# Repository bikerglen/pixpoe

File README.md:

# pixpoe
Control and power up to 20 W of neopixels or other WS2812b LEDs over ethernet!

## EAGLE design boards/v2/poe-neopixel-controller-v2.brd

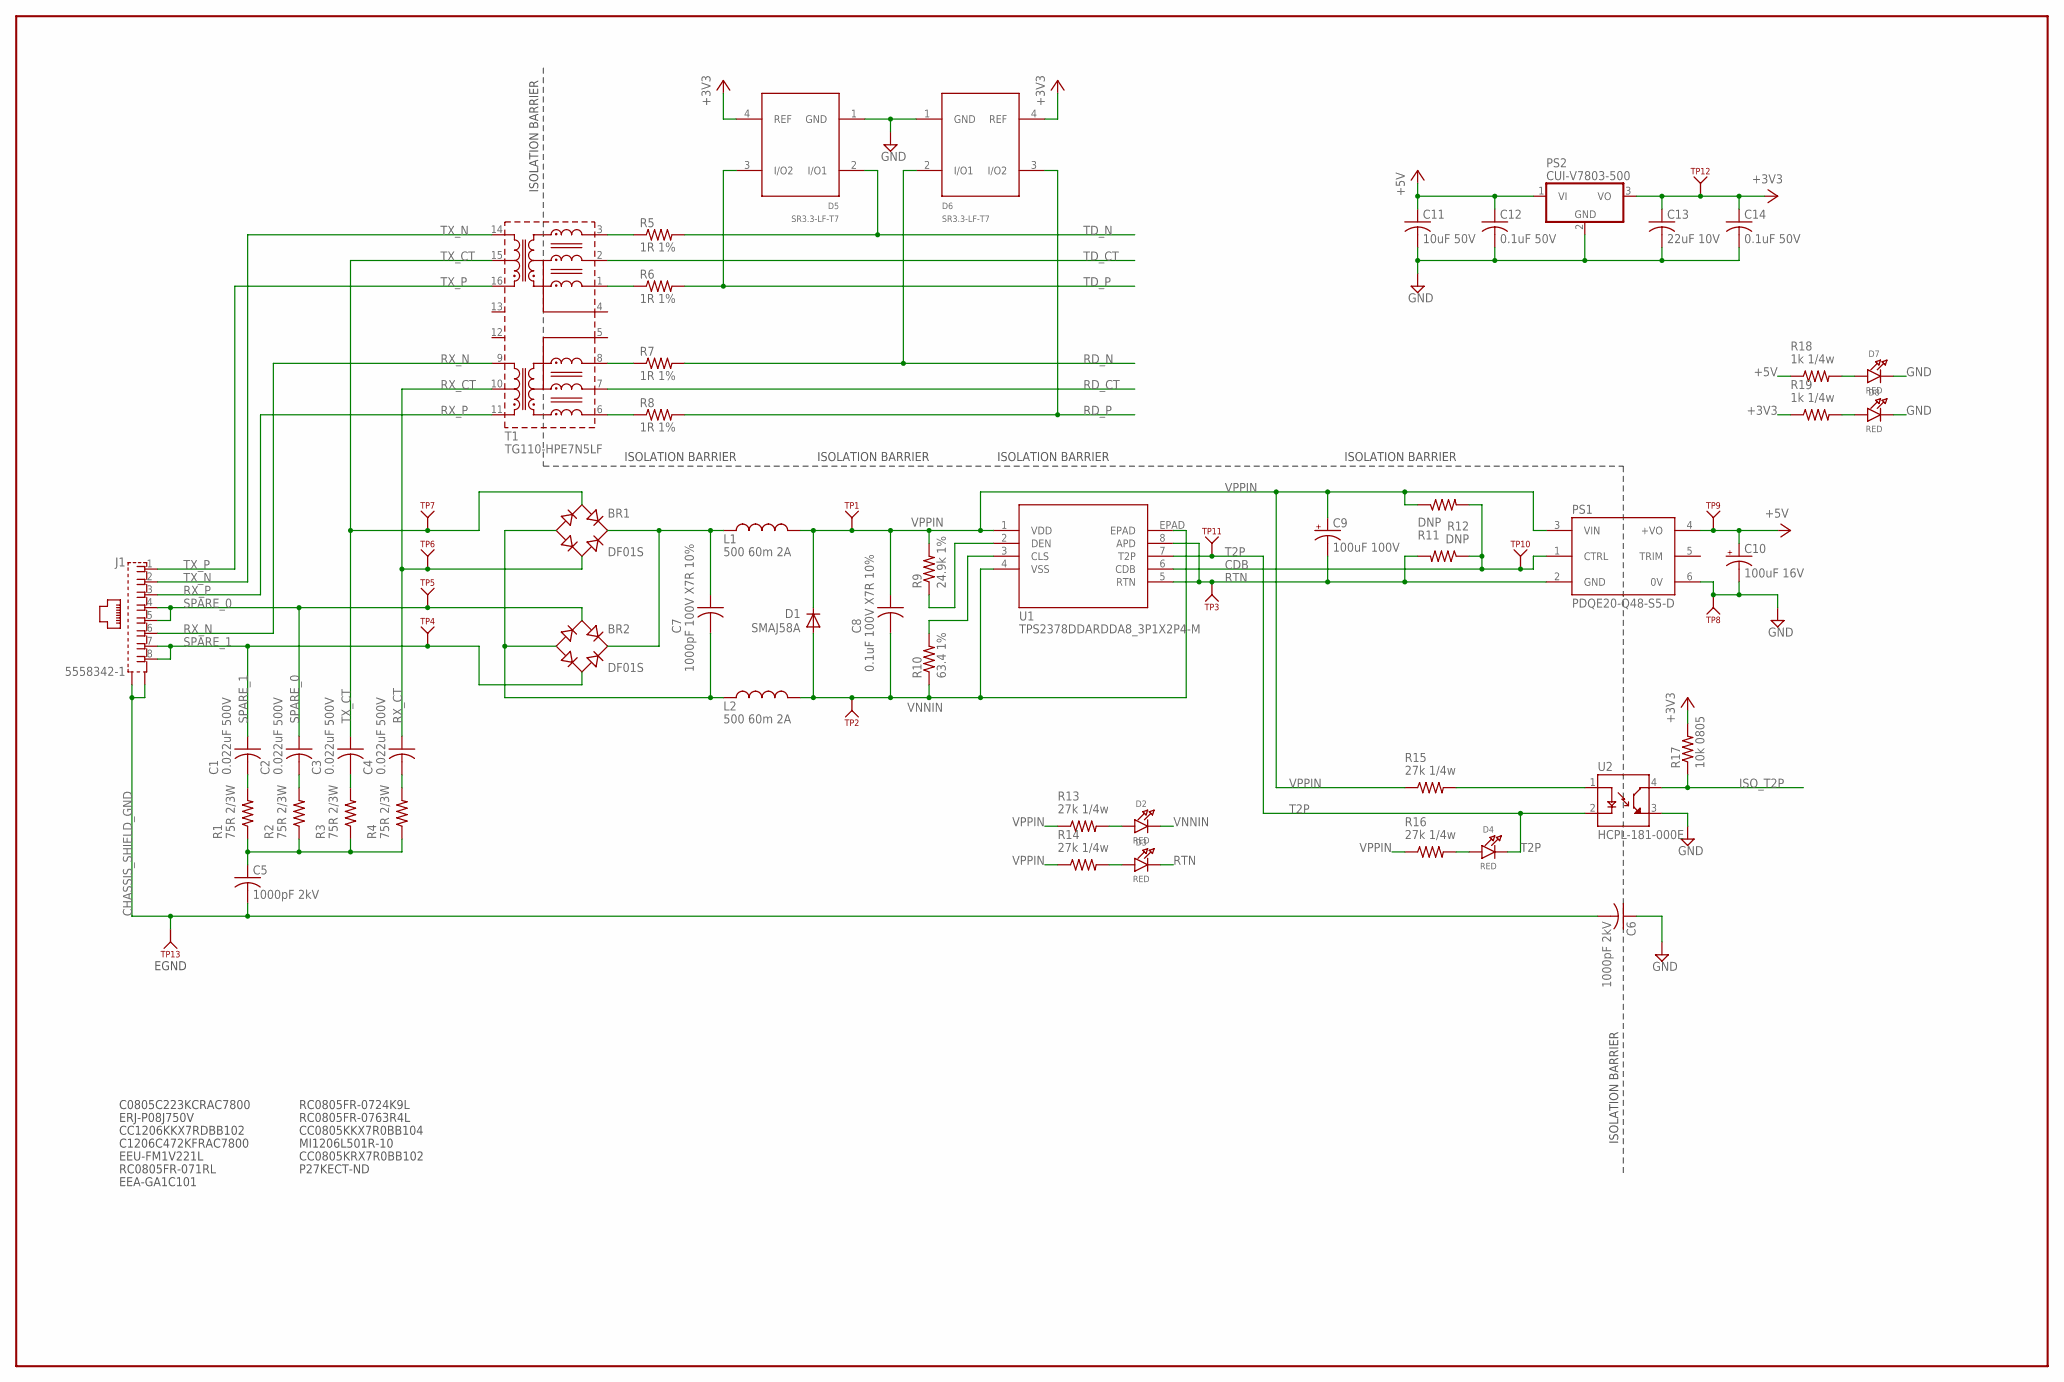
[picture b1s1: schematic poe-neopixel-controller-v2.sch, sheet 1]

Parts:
BR1, BR2: DF01S; DFS
C1, C2, C3, C4: 0.022uF 500V; C1206
C5, C6: 1000pF 2kV; C1206K
C7: 1000pF 100V X7R 10%; C0805
C8: 0.1uF 100V X7R 10%; C0805
C9: 100uF 100V; E5-10,5
C10: 100uF 16V; E2,5-7
C11: 10uF 50V; C1210K; MFR_PART_NO C1210C106K5RACTU
C12, C14: 0.1uF 50V; C0805; MFR_PART_NO C1206S104M5RACTU
C13: 22uF 10V; C1206K; MFR_PART_NO C1206C226K8RAC7800
D1: SMAJ58A; DO214AC
D2, D3, D4, D7, D8: RED; CHIPLED_0805_NOOUTLINE
D5, D6: SR3.3-LF-T7; SOT143B
J1: 5558342-1; TE_5558342-1
L1, L2: 500 60m 2A; L3216C
PS1: PDQE20-Q48-S5-D; CONV_PDQE20-Q48-S5-D
PS2: CUI-V7803-500; CUI-78XX-500
R1, R2, R3, R4: 75R 2/3W; R1206
R5, R6, R7, R8: 1R 1%; R0805
R9: 24.9k 1%; R0805
R10: 63.4 1%; R0805
R11, R12: DNP; R1206
R13, R14, R15, R16: 27k 1/4w; R1206
R17: 10k 0805; R0805
R18, R19: 1k 1/4w; R0805
T1: TG110-HPE7N5LF; RP-ULTRA
TP1, TP2, TP3, TP4, TP5, TP6, TP7, TP8, TP9, TP10, TP11, TP12, TP13: KEYSTONE_500X; KEYSTONE_TP500X
U1: TPS2378DDARDDA8_3P1X2P4-M; DDA8_3P1X2P4-M
U2: HCPL-181-000E; SOIC254P675X240-4N

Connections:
+3V3: C13.1, C14.1, D5.4 (REF), D6.4 (REF), PS2.3 (VO), R17.2, R19.1, TP12.1; also elsewhere on the board
+5V: C10.+, C11.1, C12.1, PS1.4 (+VO), PS2.1 (VI), R18.1, TP9.1; also elsewhere on the board
CDB: PS1.1 (CTRL), R11.2, R12.1, TP10.1, U1.6 (CDB)
CHASSIS_SHIELD_GND: C5.2, C6.2, J1.SH1 (S1), J1.SH2 (S2), TP13.1
GND: C6.1, C10.-, C11.2, C12.2, C13.2, C14.2, D5.1 (GND), D6.1 (GND), D7.C, D8.C, PS1.6 (0V), PS2.2 (GND), TP8.1, U2.3 (EMITTER); also elsewhere on the board
ISO_T2P: R17.1, U2.4 (COLLECTOR); also elsewhere on the board
unnamed: BR1.+, BR2.+, C7.1, L1.1
unnamed: R5.1, T1.3
unnamed: BR1.-, BR2.-, C7.2, L2.1
unnamed: R6.1, T1.1
unnamed: C4.2, R4.2
unnamed: R7.1, T1.8
unnamed: D2.A, R13.2
unnamed: R15.2, U2.1 (ANODE)
unnamed: R8.1, T1.6
unnamed: C1.2, R1.2
unnamed: C2.2, R2.2
unnamed: C3.2, R3.2
unnamed: C5.1, R1.1, R2.1, R3.1, R4.1
unnamed: R9.1, U1.2 (DEN)
unnamed: R10.2, U1.3 (CLS)
unnamed: D3.A, R14.2
unnamed: D4.A, R16.2
unnamed: D7.A, R18.2
unnamed: D8.A, R19.2
RD_CT: T1.7; also elsewhere on the board
RD_N: D6.2 (I/O1), R7.2; also elsewhere on the board
RD_P: D6.3 (I/O2), R8.2; also elsewhere on the board
RTN: C9.-, D3.C, PS1.2 (GND), R12.2, TP3.1, U1.5 (RTN), U1.8 (APD)
RX_CT: BR1.AC2, C4.1, T1.10, TP6.1
RX_N: J1.6, T1.9
RX_P: J1.3, T1.11
SPARE_0: BR2.AC1, C2.1, J1.4, J1.5, TP5.1
SPARE_1: BR2.AC2, C1.1, J1.7, J1.8, TP4.1
T2P: D4.C, TP11.1, U1.7 (T2P), U2.2 (CATHODE)
TD_CT: T1.2; also elsewhere on the board
TD_N: D5.2 (I/O1), R5.2; also elsewhere on the board
TD_P: D5.3 (I/O2), R6.2; also elsewhere on the board
TX_CT: BR1.AC1, C3.1, T1.15, TP7.1
TX_N: J1.2, T1.14
TX_P: J1.1, T1.16
VNNIN: C8.2, D1.A, D2.C, L2.2, R10.1, TP2.1, U1.4 (VSS), U1.EPAD
VPPIN: C8.1, C9.+, D1.C, L1.2, PS1.3 (VIN), R9.2, R11.1, R13.1, R14.1, R15.1, R16.1, TP1.1, U1.1 (VDD)

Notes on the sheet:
C0805C223KCRAC7800
ERJ-P08J750V
CC1206KKX7RDBB102
C1206C472KFRAC7800
EEU-FM1V221L
ISOLATION BARRIER
RC0805FR-071RL
EEA-GA1C101
RC0805FR-0724K9L
RC0805FR-0763R4L
CC0805KKX7R0BB104
MI1206L501R-10
CC0805KRX7R0BB102
P27KECT-ND
EGND

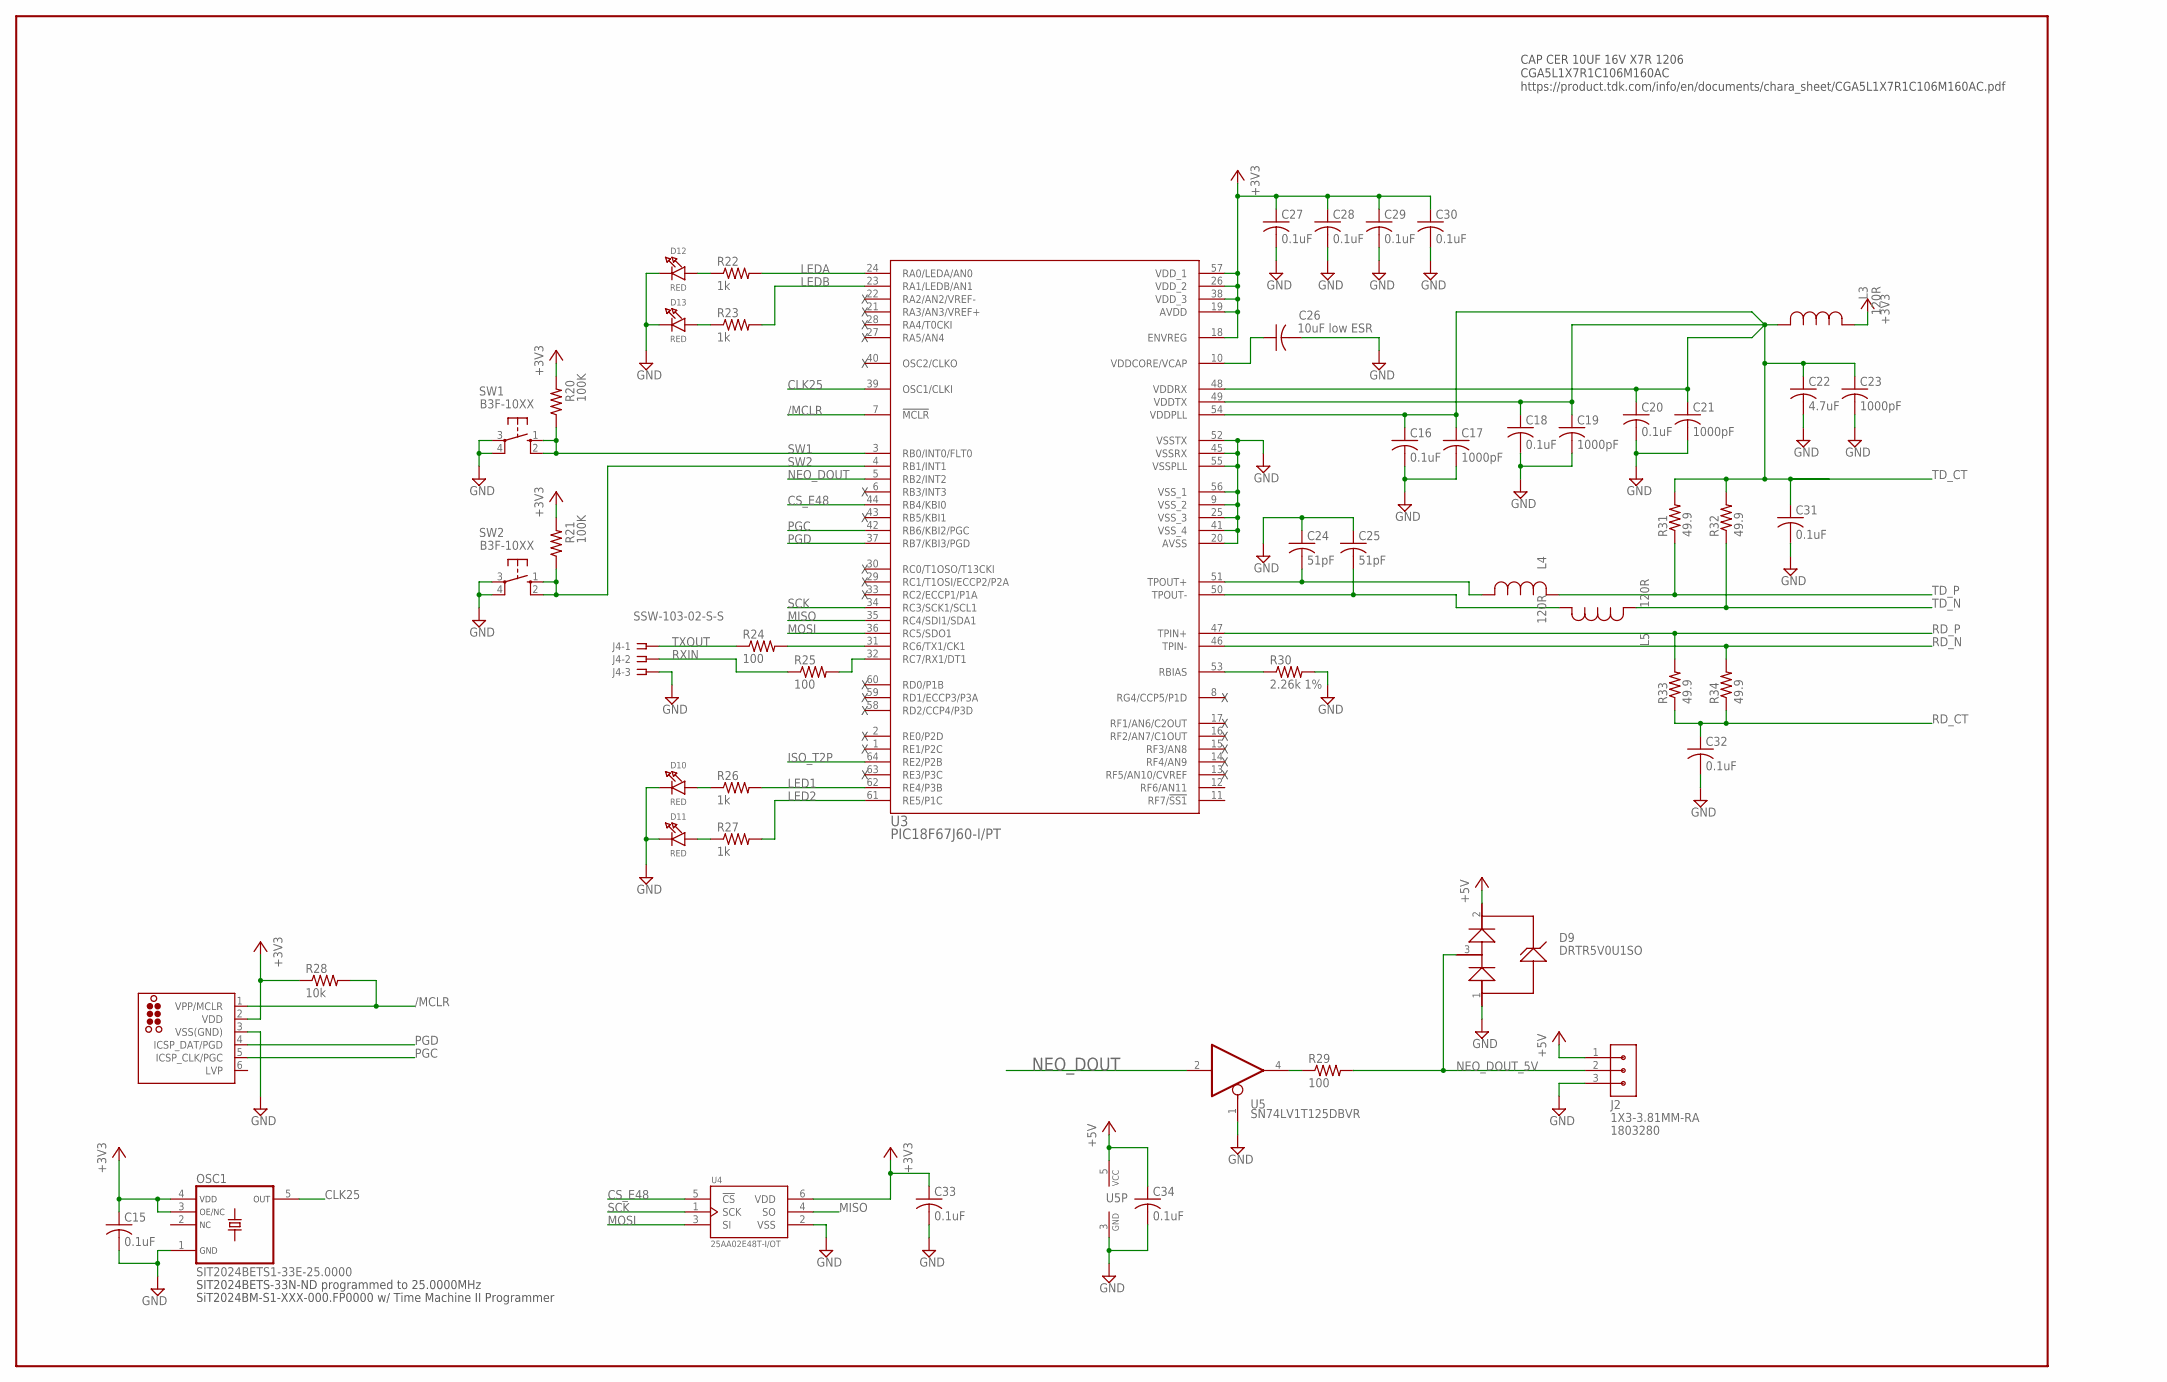
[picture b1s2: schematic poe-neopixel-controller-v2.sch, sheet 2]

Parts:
C15, C27, C28, C29, C30, C33, C34: 0.1uF; C0603
C16, C18, C20, C31, C32: 0.1uF; C0805
C17, C19, C21, C23: 1000pF; C0805
C22: 4.7uF; C0805
C24, C25: 51pF; C0805
C26: 10uF low ESR; C1206
D9: DRTR5V0U1SO; SOT23-3; MFR_PART_NO DRTR5V0U1SO
D10, D11, D12, D13: RED; CHIPLED_0805_NOOUTLINE
J2: 1X3-3.81MM-RA; CON-PHOENIX-3.81-1X3-RA; MFR_PART_NO 1803280
J3: TC2030-MCP-NL
J4: SSW-103-02-S-S
L3, L4, L5: 120R; IND_1608-M
OSC1: SIT2024BETS1-33E-25.0000; SOT23-5
R20, R21: 100K; R0805
R22, R23, R26, R27: 1k; R0805
R24, R25, R29: 100; R0805
R28: 10k; R0805
R30: 2.26k 1%; R0805
R31, R32, R33, R34: 49.9; R0805
SW1, SW2: B3F-10XX
U3: PIC18F67J60-I/PT; TQFP64_10X10MC
U4: 25AA02E48T-I/OT; SOT95P270X145-6N
U5: SN74LV1T125DBVR; SOT23-5; MFR_PART_NO SN74LV1T125DBVR

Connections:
+3V3: C15.1, C27.1, C28.1, C29.1, C30.1, C33.1, J3.2 (VDD), L3.2, OSC1.3 (OE/NC), OSC1.4 (VDD), R20.2, R21.2, R28.1, U3.18 (ENVREG), U3.19 (AVDD), U3.26 (VDD_2), U3.38 (VDD_3), U3.57 (VDD_1), U4.6 (VDD); also elsewhere on the board
+5V: C34.1, D9.2, J2.1, U5.5 (VCC); also elsewhere on the board
/MCLR: J3.1 (VPP/MCLR), R28.2, U3.7 (!MCLR)
CLK25: OSC1.5 (OUT), U3.39 (OSC1/CLKI)
CS_E48: U3.44 (RB4/KBI0), U4.5 (!CS)
DATA_5V: R29.1, U5.4 (O)
GND: C15.2, C16.2, C17.2, C18.2, C19.2, C20.2, C21.2, C22.2, C23.2, C24.1, C25.1, C26.2, C27.2, C28.2, C29.2, C30.2, C31.2, C32.2, C33.2, C34.2, D9.1 (3), D10.C, D11.C, D12.C, D13.C, J2.3, J3.3 (VSS(GND)), J4.3, OSC1.1 (GND), R30.2, SW1.3, SW1.4 (P1), SW2.3, SW2.4 (P1), U3.9 (VSS_2), U3.20 (AVSS), U3.25 (VSS_3), U3.41 (VSS_4), U3.45 (VSSRX), U3.52 (VSSTX), U3.55 (VSSPLL), U3.56 (VSS_1), U4.2 (VSS), U5.1 (OE), U5.3 (GND); also elsewhere on the board
ISO_T2P: U3.64 (RE2/P2B); also elsewhere on the board
LED1: R26.2, U3.62 (RE4/P3B)
LED2: R27.2, U3.61 (RE5/P1C)
LEDA: R22.2, U3.24 (RA0/LEDA/AN0)
LEDB: R23.2, U3.23 (RA1/LEDB/AN1)
MISO: U3.35 (RC4/SDI1/SDA1), U4.4 (SO)
MOSI: U3.36 (RC5/SDO1), U4.3 (SI)
unnamed: C26.1, U3.10 (VDDCORE/VCAP)
unnamed: R30.1, U3.53 (RBIAS)
unnamed: D13.A, R23.1
unnamed: D10.A, R26.1
unnamed: D11.A, R27.1
unnamed: D12.A, R22.1
NEO_DOUT: U3.5 (RB2/INT2), U5.2 (I)
NEO_DOUT_5V: D9.3 (1), J2.2, R29.2
PGC: J3.5 (ICSP_CLK/PGC), U3.42 (RB6/KBI2/PGC)
PGD: J3.4 (ICSP_DAT/PGD), U3.37 (RB7/KBI3/PGD)
RD_CT: C32.1, R33.1, R34.1; also elsewhere on the board
RD_N: R34.2, U3.46 (TPIN-); also elsewhere on the board
RD_P: R33.2, U3.47 (TPIN+); also elsewhere on the board
RXD: R25.2, U3.32 (RC7/RX1/DT1)
RXIN: J4.2, R25.1
SCK: U3.34 (RC3/SCK1/SCL1), U4.1 (SCK)
SW1: R20.1, SW1.1 (S), SW1.2 (S1), U3.3 (RB0/INT0/FLT0)
SW2: R21.1, SW2.1 (S), SW2.2 (S1), U3.4 (RB1/INT1)
TDF_N: C25.2, L5.1, U3.50 (TPOUT-)
TDF_P: C24.2, L4.1, U3.51 (TPOUT+)
TD_CT: C16.1, C17.1, C18.1, C19.1, C20.1, C21.1, C22.1, C23.1, C31.1, L3.1, R31.2, R32.2, U3.48 (VDDRX), U3.49 (VDDTX), U3.54 (VDDPLL); also elsewhere on the board
TD_N: L5.2, R32.1; also elsewhere on the board
TD_P: L4.2, R31.1; also elsewhere on the board
TXD: R24.2, U3.31 (RC6/TX1/CK1)
TXOUT: J4.1, R24.1

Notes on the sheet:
SIT2024BETS-33N-ND programmed to 25.0000MHz
SiT2024BM-S1-XXX-000.FP0000 w/ Time Machine II Programmer
CAP CER 10UF 16V X7R 1206 CGA5L1X7R1C106M160AC https://product.tdk.com/info/en/documents/chara_sheet/CGA5L1X7R1C106M160AC.pdf

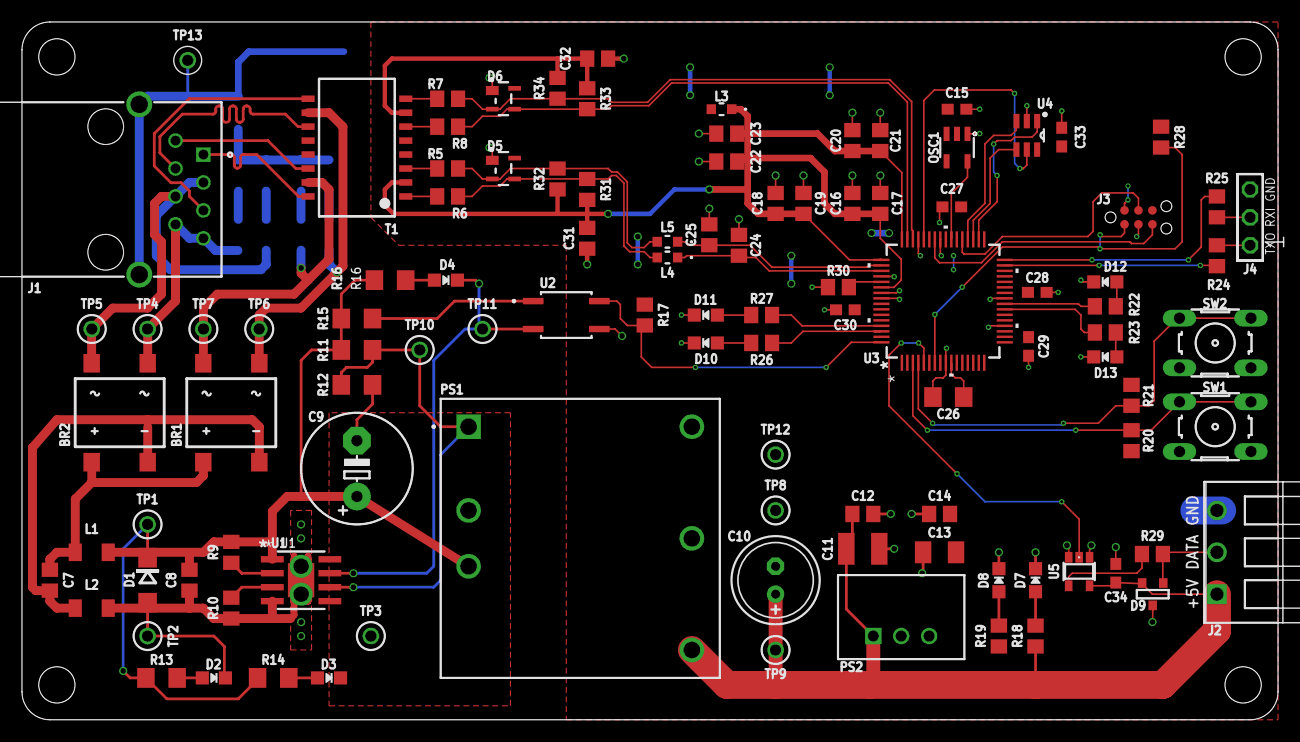
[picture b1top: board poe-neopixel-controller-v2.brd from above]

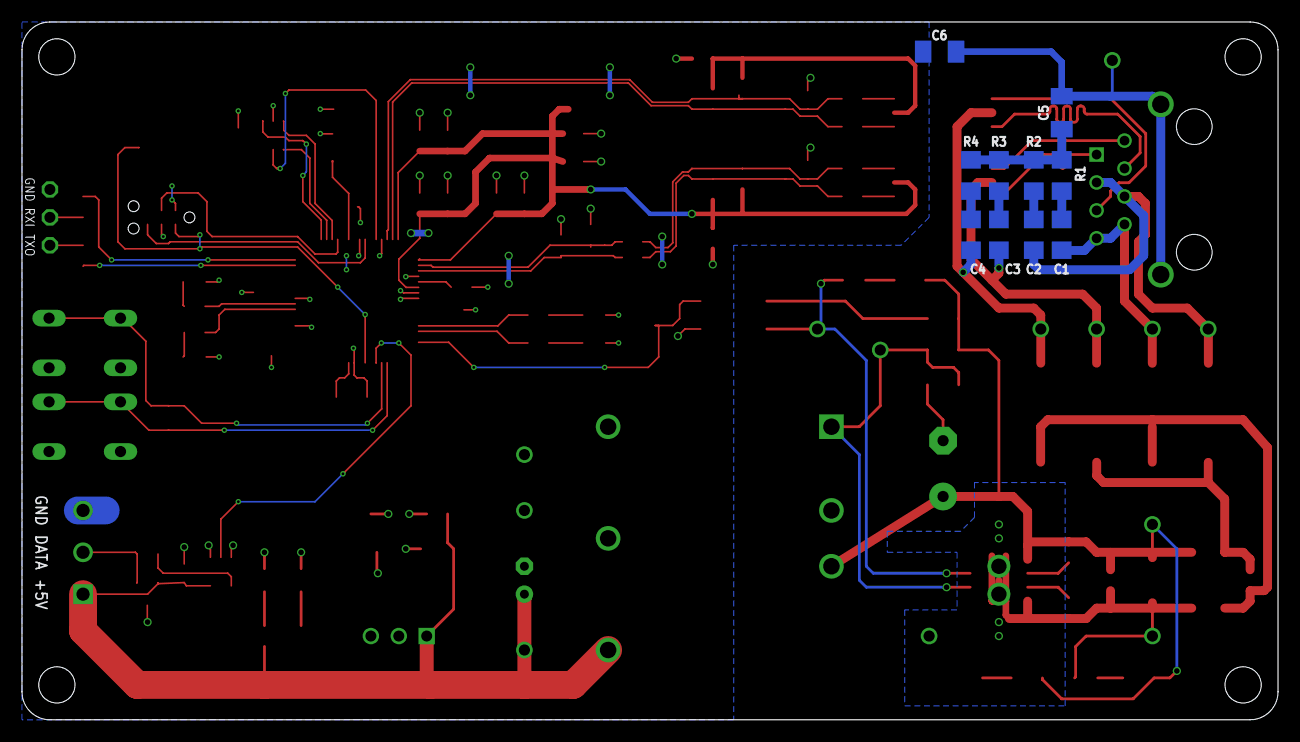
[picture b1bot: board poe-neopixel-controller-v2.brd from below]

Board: 2 copper layers, 114.3 x 63.5 mm, 116 parts (10 on the bottom side), 72 nets.

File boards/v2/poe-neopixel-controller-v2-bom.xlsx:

Qty | Parts | Description | Size | Mfr | Mfr Part # | Dist | Dist Part 3 | Notes
2 | BR1, BR2 | BRIDGE RECT 1P 100V 1.5A SMD 4SDIP | --- | On Semiconductor | DF01S | Digi-Key | DF01SCT-ND
4 | C1, C2, C3, C4 | CAP CER 0.022uF 500V 10% X7R SMD 1206 | 1206 | Johanson Dielectrics | 501R18W223KV4E | Digi-Key | 709-1028-1-ND
2 | C5, C6 | CAP CER 1000pF 2KV 10% X7R SMD 1206 | 1206 | Johanson Dielectrics | 202R18W102KV4E | Digi-Key | 709-1036-1-ND
1 | C7 | CAP CER 1000PF 100V 10% X7R SMD 0805 | 0805 | Kemet | C0805C102K1RACTU | Digi-Key | 399-1148-1-ND
1 | C8 | CAP CER 0.1uF 100V 10% X7R SMD 0805 | 0805 | Yageo | CC0805KKX7R0BB104 | Digi-Key | 311-2083-1-ND
1 | C9 | CAP ALUM 100uF 20% 100V RADIAL | E5-10,5 | Panasonic | ECA-2AHG101 | Digi-Key | P5597-ND
1 | C10 | CAP ALUM 100uF 20% 16V RADIAL | E2,5-7 | Panasonic | EEA-GA1C101H | Digi-Key | P15797CT-ND
1 | C11 | CAP CER 10uF 50V 10% X7R SMD 1210 | 1210 | Kemet | C1210C106K5RACTU | Digi-Key | 399-11629-1-ND
7 | C12, C14, C16, C18, C20, C31, C32 | CAP CER 0.1u 50V 10% X7R SMD 0805 | 0805 | Kemet | C0805C104K5RACTU | Digi-Key | 399-1170-1-ND
1 | C13 | CAP CER 22uF 10V 10% X7R SMD 1206 | 1206 | Kemet | C1206C226K8RAC7800 | Digi-Key | 399-11947-1-ND
7 | C15, C27, C28, C29, C30, C33, C34 | CAP CER 0.1uF 50V 20% X7R SMD 0603 | 0603 | TDK | C1608X7R1H104M | Digi-Key | 445-5098-1-ND
4 | C17, C19, C21, C23 | CAP CER 1000pF 50V 20% X7R SMD 0805 | 0805 | Kemet | C0805C102M5RACTU | Digi-Key | 399-1146-1-ND
1 | C22 | CAP CER 4.7uF 10V 10% X5R SMD 0805 | 0805 | Kemet | C0805C475K8PACTU | Digi-Key | 399-3133-1-ND
2 | C24, C25 | CAP CER 51pF 50V 5% NP0 SMD 0805 | 0805 | Yageo | CC0805JRNPO9BN510 | Digi-Key | 311-4239-1-ND
1 | C26 | CAP CER 10uF 16V 20% X7R SMD 1206 | 1206 | TDK | CGA5L1X7R1C106M160AC | Digi-Key | 445-12903-1-ND
1 | D1 | TVS DIODE 58V 121V SMA | --- | ST Microelectronics | SMAJ58A-TR | Digi-Key | 497-3508-1-ND
9 | D2, D3, D4, D7, D8, D10, D11, D12, D13 | LED RED CLEAR CHIP SMD 0805 | 0805 | Kingbright | APHCM2012SURCK-F01 | Digi-Key | 754-1097-1-ND
2 | D5, D6 | TVS DIODE 3.3V 7V SOT143 | --- | Bourns | CD143A-SR3.3 | Digi-Key | CD143A-SR3.3CT-ND
1 | D9 | TVS DIODE 5.5V SOT23 | --- | Diodes Inc | DRTR5V0U1SO-7 | Digi-Key | DRTR5V0U1SO-7DICT-ND
1 | J1 | CONN MOD JACK 8P8C R/A SHIELDED | --- | TE Connectivity | 5558342-1 | Digi-Key | A31466-ND
1 | J2 | TERM BLOCK HDR 3POS 90DEG 3.81MM | --- | Phoenix | 1803280 | Digi-Key | 277-1207-ND
1 | J3 | TAG CONNECT ICSP PCB PADS | --- | --- | --- | --- | ---
1 | J4 | CONN HEADER VERT 3POS 2.54MM | --- | Samtec | TSW-103-07-G-S | Digi-Key | SAM1029-03-ND
2 | L1, L2 | FERRITE BEAD 500 OHM 1206 1LN | M3216 | Laird | MI1206L501R-10 | Digi-Key | 240-2407-1-ND
3 | L3, L4, L5 | FERRITE BEAD 120 OHM 0603 1LN | M1608 | TDK | MMZ1608B121CTAH0 | Digi-Key | 445-2164-1-ND
1 | OSC1 | MEMS OSC PROG XO LVCMOS 3.3V | --- | Si Time | SIT2024BETS-33N | Digi-Key | SIT2024BETS-33N-ND | 25.0000 MHz
1 | PS1 | DC-DC ISOLATED, 20 W, 18-75 VDC | --- | Cui | PDQE20-Q48-S5-D | Digi-Key | 102-6272-ND
1 | PS2 | DC DC CONVERTER 3.3V 1.65W | --- | Cui | V7803-500 | Digi-Key | 102-1708-ND
4 | R1, R2, R3, R4 | RES SMD 75 OHM 5% 2/3W 1206 | 1206 | Panasonic | ERJ-P08J750V | Digi-Key | P75ALCT-ND
1 | R10 | RES SMD 63.4 OHM 1% 1/8W 0805 | 0805 | Panasonic | ERJ-6ENF63R4V | Digi-Key | P63.4CCT-ND
2 | R11, R12 | DNP | 1206 | --- | --- | --- | ---
4 | R13, R14, R15, R16 | RES SMD 27K OHM 5% 1/4W 1206 | 1206 | Panasonic | ERJ-8GEYJ273V | Digi-Key | P27KECT-ND
2 | R17, R28 | RES SMD 10K OHM 5% 1/8W 0805 | 0805 | Panasonic | ERJ-6GEYJ103V | Digi-Key | P10KACT-ND
6 | R18, R19, R22, R23, R26, R27 | RES SMD 1K OHM 5% 1/8W 0805 | 0805 | Panasonic | ERJ-6GEYJ102V | Digi-Key | P1.0KACT-ND
2 | R20, R21 | RES SMD 100K OHM 5% 1/8W 0805 | 0805 | Panasonic | ERJ-6GEYJ104V | Digi-Key | P100KACT-ND
3 | R24, R25, R29 | RES SMD 100 OHM 5% 1/8W 0805 | 0805 | Panasonic | ERJ-6GEYJ101V | Digi-Key | P100ACT-ND
1 | R30 | RES SMD 2.26K OHM 1% 1/8W 0805 | 0805 | Panasonic | ERJ-6ENF2261V | Digi-Key | P2.26KCCT-ND
4 | R31, R32, R33, R34 | RES SMD 49.9 OHM 1% 1/8W 0805 | 0805 | Panasonic | ERJ-6ENF49R9V | Digi-Key | P49.9CCT-ND
4 | R5, R6, R7, R8 |  | 0805 | Panasonic | ERJ-6RQF1R0V | Digi-Key | P1.0DCT-ND
1 | R9 | RES SMD 24.9K OHM 1% 1/8W 0805 | 0805 | Panasonic | ERJ-6ENF2492V | Digi-Key | P24.9KCCT-ND
2 | SW1, SW2 | SWITCH TACTILE SPST-NO 0.05A 24V | --- | Omron | B3F-1000 | Digi-Key | SW400-ND
1 | T1 | 10/100BASE-TX SMD Ultra PoE+ | --- | Halo Electronics | TG110-HPE7N5LF | Mouser | 493-TG110-HPE7N5LF
12 | TP1, TP2, TP3, TP4, TP5, TP6, TP7, TP8, TP9, TP10, TP11, TP12 | PC TEST POINT MINIATURE | --- | Keystone | 5000 | Digi-Key | 36-5000-ND
1 | U1 | IC POE CNTRL 1 CHANNEL 8SOPWR | --- | Texas Instruments | TPS2378DDAR | Digi-Key | 296-41726-1-ND
1 | U2 | OPTOISO 3.75KV TRANSISTOR 4SOIC | --- | Broadcom | HCPL-181-000E | Digi-Key | 516-1646-1-ND
1 | U3 | IC MCU 8BIT 128KB FLASH 64TQFP | --- | Microchip | PIC18F67J60-I/PT | Digi-Key | PIC18F67J60-I/PT-ND
1 | U4 | IC EEPROM 2K SPI 10MHZ SOT23-6 | --- | Microchip | 25AA02E48T-I/OT | Digi-Key | 25AA02E48T-I/OTCT-ND
1 | U5 | IC BUF NON-INVERT 5.5V SOT23-5 | --- | Texas Instruments | SN74LV1T125DBVR | Digi-Key | 296-37172-1-ND
1 | --- | TERM BLOCK PLUG 3POS STR 3.81MM | --- | Phoenix | 1803581 | Digi-Key | 277-1162-ND
1 | --- | DC-DC ISOLATED, 10 W, 18-75 VDC | --- | Cui | PDQE10-Q48-S5-T | Digi-Key | 102-4842-ND

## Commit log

2019-11-24 initial checkin
2019-11-24 moved to directory with date
2019-11-24 moved files to directory with date
2020-01-02 checkin bom

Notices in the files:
parts and their libraries:
tag-connect: ©2009 ROFA.cz - modified and updated by Robert Darlington ‹rdarlington@gmail.com›
microbuilder: This work is placed in the public domain, and may be freely used for commercial and non-commercial work with the following conditions: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
